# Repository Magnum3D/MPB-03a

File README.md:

MPB-03a
===========
Reprap Electronics for Magnum printers based on Printrboard

Отличия платы:

1. Плата питается напряжением 24 вольта (стол, экструдер и двигатели)
2. Установлен ЦАП для регулировки тока двигателей командами G-кода (как в версии F и исправлены ошибки).
3. Для питания вентиляторов добавлен дополнительный импульсный преобразователь на 12 вольт
4. Добавлено 4 мосфета с обвязкой - 2 для вентиляторов и 2 для светодиодных лент.
5. Заменены разъемы питания и нагревательного стола на мощные разъемы Molex.
6. Добавлен внешний разъем DSUB и на него выведено питание, ножки процессора и шина I2C
7. Мелкие исправления, доработки.

Постоянно ведется работа над усовершенствованием и доработкой платы, поэтому версия установленная в конкретный эксземпляр принтера может незначительно отличаться.

For more info see the Reprap wiki page http://reprap.org/wiki/Printrboard

The BoM with Digikey P/N's is available here: http://goo.gl/hQNEm

This project, and all of its design files (including the layout), is licensed under the [Creative Commons Attribution-ShareAlike 3.0 Unported](http://creativecommons.org/licenses/by-sa/3.0/) license.

Anyone found to be in violation of this license may not produce or discribute any products using these designs, and will have legal action taken against them.

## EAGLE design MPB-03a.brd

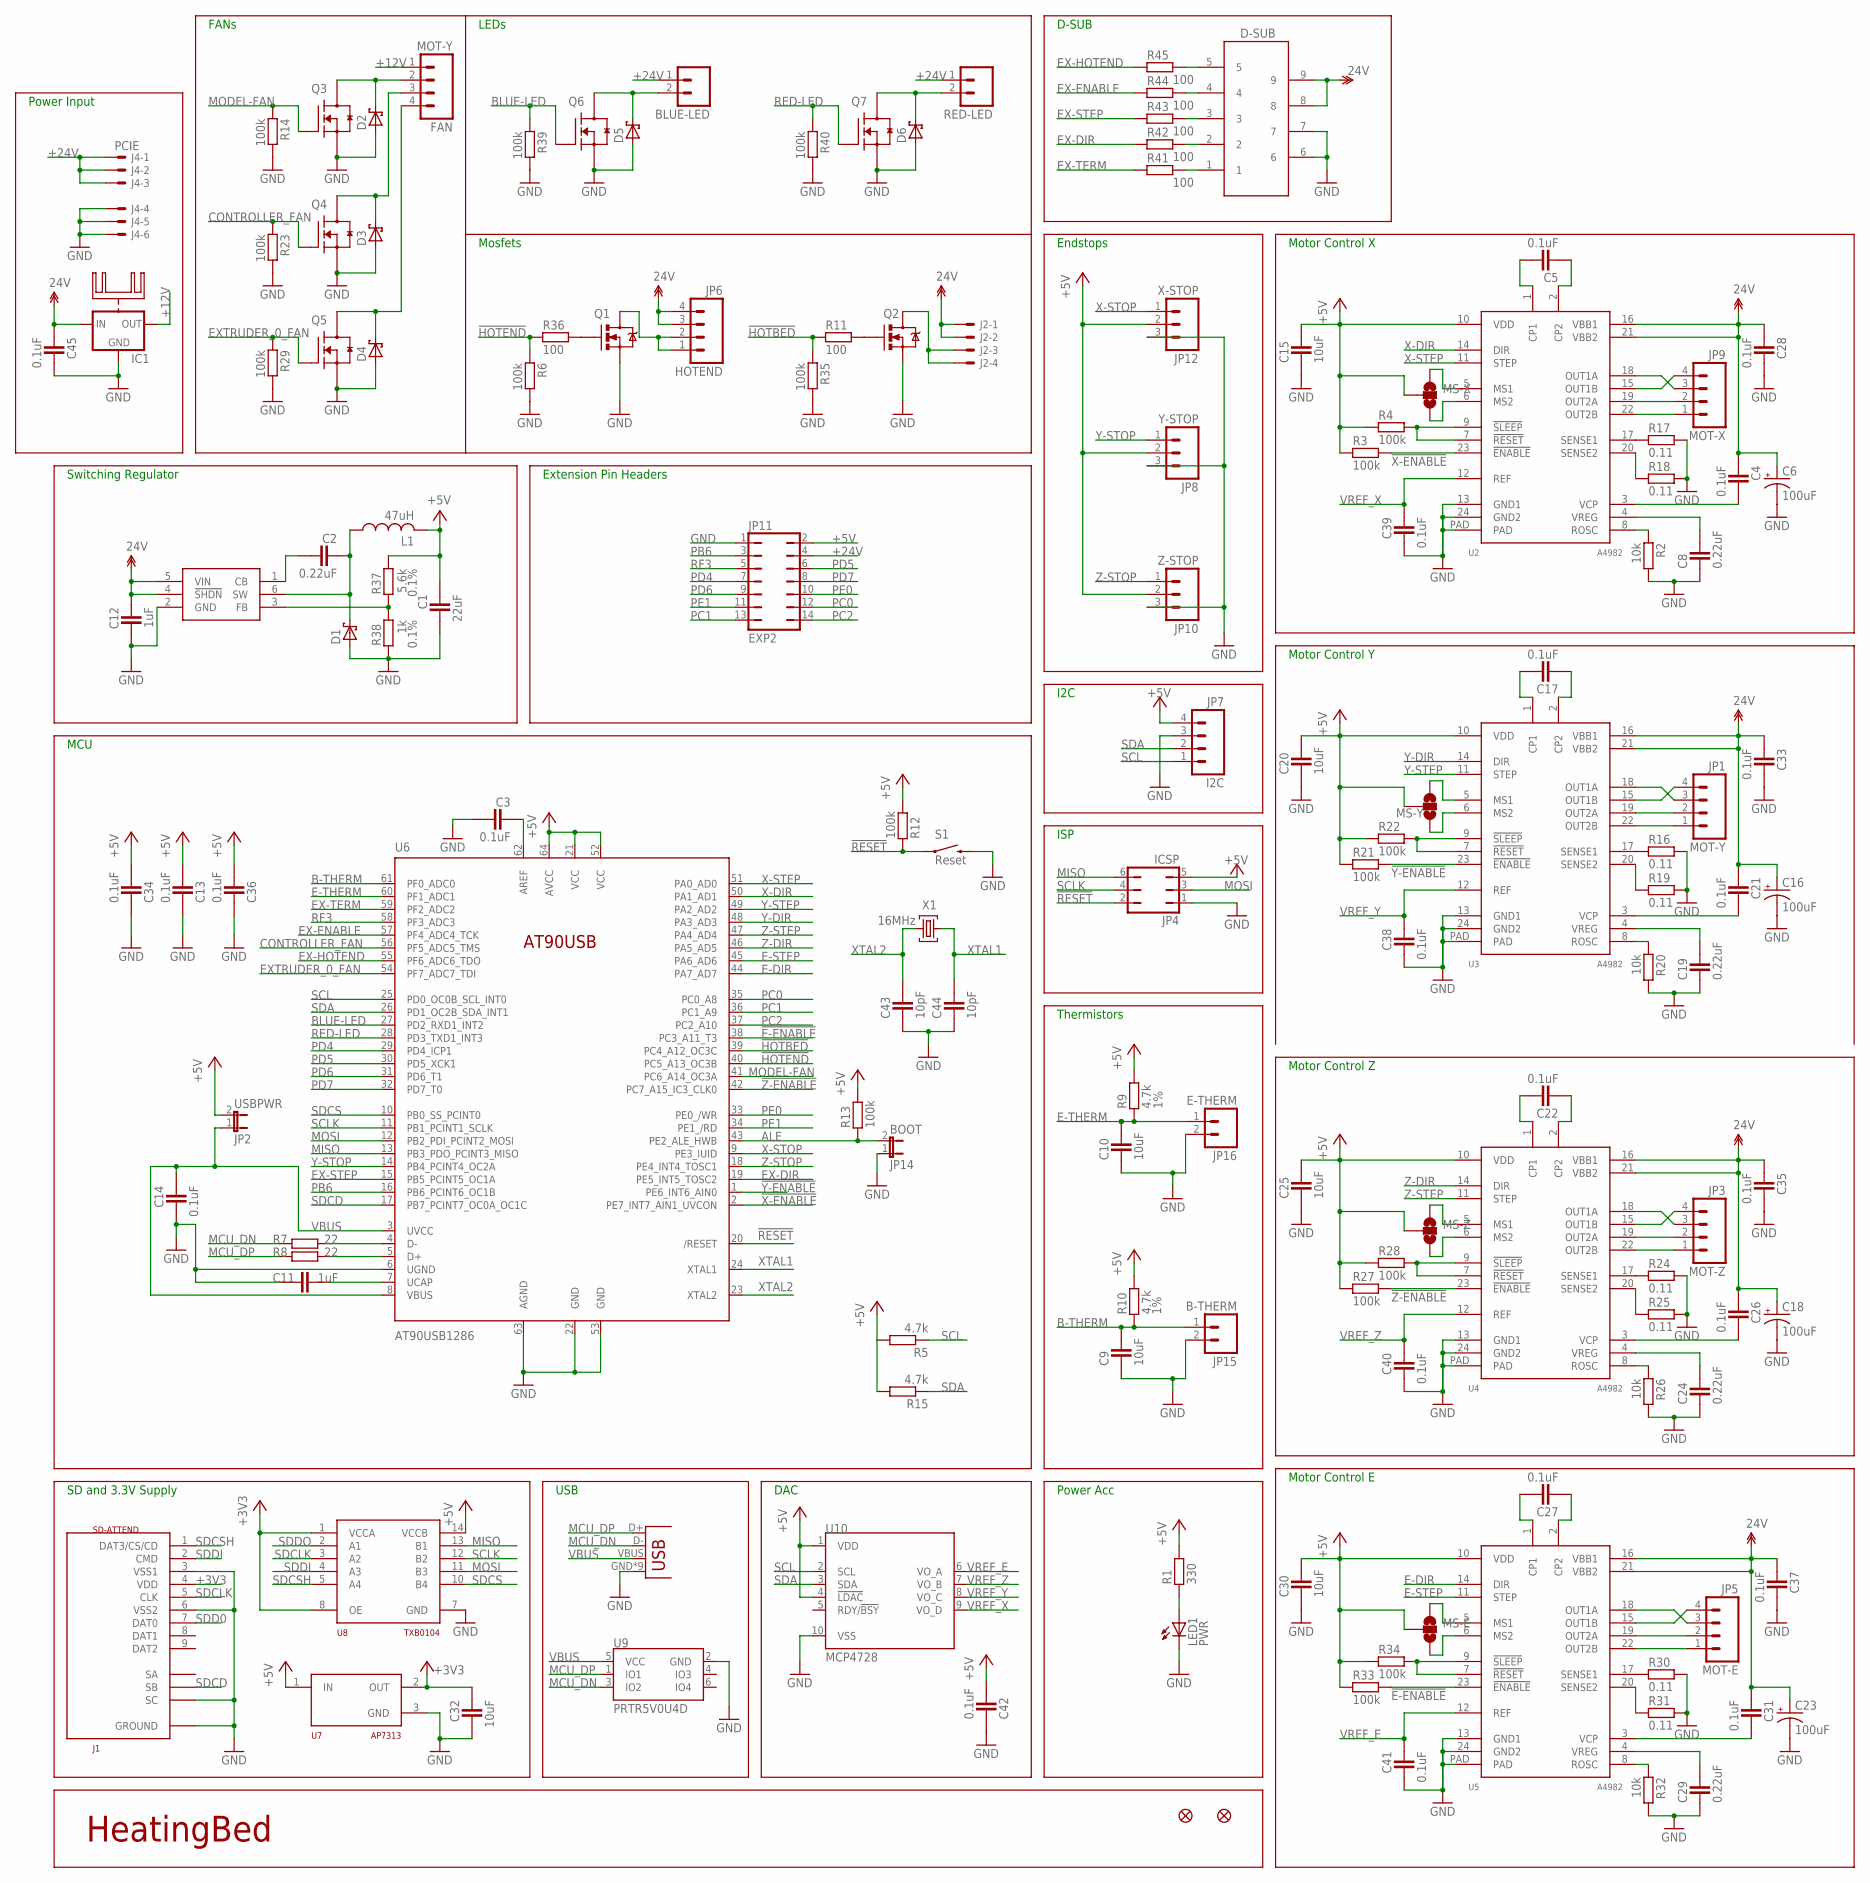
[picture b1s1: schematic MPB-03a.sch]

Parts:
BLUE-LED: M02POLAR; MOLEX-1X2
C1: 22uF; CAPC2012X145AN
C2, C8, C19, C24, C29: 0.22uF; CAPC2012X145AN
C3, C4, C5, C13, C14, C17, C21, C22, C26, C27, C28, C31, C33, C34, C35, C36, C37, C38, C39, C40, C41, C42, C45: 0.1uF; CAPC2012X145AN
C6, C16, C18, C23: 100uF; PANASONIC_D
C9, C10, C15, C20, C25, C30, C32: 10uF; CAPC2012X145AN
C11, C12: 1uF; CAPC2012X145AN
C43, C44: 10pF; CAPC2012X145AN
D1, D2, D3, D4, D5, D6: SCH-DIODESMA; SMA
D-SUB: 618009211721
FAN: MOT-Y; MOLEX-1X4
IC1: 78XXH; TO220-15X17X25
J1: SD-ATTEND
J2: 5566-4
J3: USB-MICRO-PTH; USB-MICROB-PTH
J4: PCIE; 5566-6
JP1: MOT-Y; MOLEX-1X4
JP2: USBPWR; 1X02
JP3: MOT-Z; MOLEX-1X4
JP4: ICSP; JP3Q
JP5: MOT-E; MOLEX-1X4
JP6: HOTEND; MOLEX-1X4
JP7: I2C; MOLEX-1X4
JP8: Y-STOP; MOLEX-1X3
JP9: MOT-X; MOLEX-1X4
JP10: Z-STOP; MOLEX-1X3
JP11: EXP2; JP7Q
JP12: X-STOP; MOLEX-1X3
JP14: BOOT; 1X02
JP15: B-THERM; 1X02
JP16: E-THERM; 1X02
JP26, JP33: FIDUCIAL1X2.5; FIDUCIAL-1X2.5
L1: 47uH; SDR1006
LED1: PWR; CHIP-LED0805
MS-E: SOLDERJUMPER_2WAYCONNECTED; SJ_3_CONNECTED
MS-X: SOLDERJUMPER_2WAYCONNECTED; SJ_3_CONNECTED
MS-Y: SOLDERJUMPER_2WAYCONNECTED; SJ_3_CONNECTED
MS-Z: SOLDERJUMPER_2WAYCONNECTED; SJ_3_CONNECTED
Q1, Q2: RFP30N06LE; TO220V
Q3, Q4, Q5, Q6, Q7: RFP30N06LE; SOT95P280X135-3N
R1: 330; RESC2012X70N
R2, R20, R26, R32: 10k; RESC2012X70N
R3, R4, R6, R12, R13, R14, R21, R22, R23, R27, R28, R29, R33, R34, R35, R39, R40: 100k; RESC2012X70N
R5, R15: 4.7k; RESC2012X70N
R7, R8: 22; RESC2012X70N
R9, R10: 4.7k; RESC2012X70N; TOLERANCE 1%
R11, R36, R41, R42, R43, R44, R45: 100; RESC2012X70N
R16, R17, R18, R19, R24, R25, R30, R31: 0.11; RESC2012X70N
R37: 5.6k; RESC2012X70N; TOLERANCE 0.1%
R38: 1k; RESC2012X70N; TOLERANCE 0.1%
RED-LED: M02POLAR; MOLEX-1X2
S1: Reset; TACTILE_SWITCH_TALL
U1: LM2841; TSOT6
U2, U3, U4, U5: A4982; TSSOP-24
U6: AT90USB1286; TQFP64-2
U7: AP7313; SOT23C
U8: TXB0104; TSSOP14
U9: PRTR5V0U4D; SOT23-6
U10: MCP4728; MSOP10
X1: 16MHz; NDK-XTAL

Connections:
!E-ENABLE: R33.2, U5.23 (!ENABLE), U6.38 (PC3_A11_T3)
!HOTBED: R11.1, R35.1, U6.39 (PC4_A12_OC3C)
!HOTEND: R6.1, R36.1, U6.40 (PC5_A13_OC3B)
!RESET: JP4.2, R12.1, S1.A2 (1), U6.20 (/RESET)
!X-ENABLE: R3.2, U2.23 (!ENABLE), U6.2 (PE7_INT7_AIN1_UVCON)
!Y-ENABLE: R21.2, U3.23 (!ENABLE), U6.1 (PE6_INT6_AIN0)
!Z-ENABLE: R27.2, U4.23 (!ENABLE), U6.42 (PC7_A15_IC3_CLK0)
+3V3: C32.1, J1.4 (VDD), U7.2 (OUT), U8.1 (VCCA), U8.8 (OE)
+5V: C1.1, C13.2, C15.2, C20.2, C25.2, C30.2, C34.2, C36.2, C42.2, JP2.2, JP4.5, JP7.4, JP8.2, JP10.2, JP11.2, JP12.2, L1.P$2 (2), MS-E.2, MS-X.2, MS-Y.2, MS-Z.2, R1.2, R3.1, R4.1, R5.2, R9.2, R10.2, R12.2, R13.2, R15.2, R21.1, R22.1, R27.1, R28.1, R33.1, R34.1, R37.1, U2.10 (VDD), U3.10 (VDD), U4.10 (VDD), U5.10 (VDD), U6.21 (VCC), U6.52 (VCC), U6.64 (AVCC), U7.1 (IN), U8.14 (VCCB), U10.1 (VDD), U10.4 (!LDAC)
+12V: FAN.1, IC1.OUT
+24V: BLUE-LED.1, C4.1, C6.+, C12.1, C16.+, C18.+, C21.1, C23.+, C26.1, C28.1, C31.1, C33.1, C35.1, C37.1, C45.1, D-SUB.8, D-SUB.9, IC1.IN, J2.1, J2.2, J4.1, J4.2, J4.3, JP6.3, JP6.4, JP11.4, RED-LED.1, U1.4 (!SHDN), U1.5 (VIN), U2.16 (VBB1), U2.21 (VBB2), U3.16 (VBB1), U3.21 (VBB2), U4.16 (VBB1), U4.21 (VBB2), U5.16 (VBB1), U5.21 (VBB2)
ALE: JP14.2, R13.1, U6.43 (PE2_ALE_HWB)
AREF: C3.1, U6.62 (AREF)
B-THERM: C9.2, JP15.1, R10.1, U6.61 (PF0_ADC0)
BLUE-LED: Q6.1 (G), R39.1, U6.27 (PD2_RXD1_INT2)
CONTROLLER_FAN: Q4.1 (G), R23.1, U6.56 (PF5_ADC5_TMS)
E-DIR: U5.14 (DIR), U6.44 (PA7_AD7)
E-STEP: U5.11 (STEP), U6.45 (PA6_AD6)
E-THERM: C10.2, JP16.1, R9.1, U6.60 (PF1_ADC1)
EX-DIR: R42.1, U6.19 (PE5_INT5_TOSC2)
EX-ENABLE: R44.1, U6.57 (PF4_ADC4_TCK)
EX-HOTEND: R45.1, U6.55 (PF6_ADC6_TDO)
EX-STEP: R43.1, U6.15 (PB5_PCINT5_OC1A)
EX-TERM: R41.1, U6.59 (PF2_ADC2)
EXTRUDER_0_FAN: Q5.1 (G), R29.1, U6.54 (PF7_ADC7_TDI)
GND: C1.2, C3.2, C6.-, C8.1, C9.1, C10.1, C11.1, C12.2, C13.1, C14.2, C15.1, C16.-, C18.-, C19.1, C20.1, C23.-, C24.1, C25.1, C28.2, C29.1, C30.1, C32.2, C33.2, C34.1, C35.2, C36.1, C37.2, C38.2, C39.2, C40.2, C41.2, C42.1, C43.1, C44.1, C45.2, D1.A, D2.A, D3.A, D4.A, D5.A, D6.A, D-SUB.6, D-SUB.7, IC1.GND, J1.3 (VSS1), J1.6 (VSS2), J1.G (GROUND), J1.SC, J3.GND, J3.GND1 (GND), J3.GND2 (GND), J3.GND3 (GND), J3.GND4 (GND), J3.GND5 (GND), J3.GND6 (GND), J3.GND7 (GND), J3.GND8 (GND), J4.4, J4.5, J4.6, JP4.1, JP7.3, JP8.3, JP10.3, JP11.1, JP12.3, JP14.1, JP15.2, JP16.2, LED1.C, Q1.3 (S), Q2.3 (S), Q3.2 (S), Q4.2 (S), Q5.2 (S), Q6.2 (S), Q7.2 (S), R2.2, R6.2, R14.2, R16.2, R17.2, R18.2, R19.2, R20.2, R23.2, R24.2, R25.2, R26.2, R29.2, R30.2, R31.2, R32.2, R35.2, R38.2, R39.2, R40.2, S1.B2 (2), U1.2 (GND), U2.13 (GND1), U2.24 (GND2), U2.PAD, U3.13 (GND1), U3.24 (GND2), U3.PAD, U4.13 (GND1), U4.24 (GND2), U4.PAD, U5.13 (GND1), U5.24 (GND2), U5.PAD, U6.6 (UGND), U6.22 (GND), U6.53 (GND), U6.63 (AGND), U7.3 (GND), U8.7 (GND), U9.2 (GND), U10.10 (VSS)
HOTBED-GND: J2.3, J2.4, Q2.2 (D)
HOTEND-GND: JP6.1, JP6.2, Q1.2 (D)
MCU_DN: J3.D-, R7.1, U9.3 (IO2)
MCU_DP: J3.D+, R8.1, U9.1 (IO1)
MISO: JP4.6, U6.13 (PB3_PDO_PCINT3_MISO), U8.13 (B1)
MODEL-FAN: Q3.1 (G), R14.1, U6.41 (PC6_A14_OC3A)
MOSI: JP4.3, U6.12 (PB2_PDI_PCINT2_MOSI), U8.11 (B3)
unnamed: LED1.A, R1.1
unnamed: D2.C, FAN.2, Q3.3 (D)
unnamed: R7.2, U6.4 (D-)
unnamed: R8.2, U6.5 (D+)
unnamed: D3.C, FAN.3, Q4.3 (D)
unnamed: D4.C, FAN.4, Q5.3 (D)
unnamed: Q2.1 (G), R11.2
unnamed: BLUE-LED.2, D5.C, Q6.3 (D)
unnamed: C11.2, U6.7 (UCAP)
unnamed: JP9.3, U2.18 (OUT1A)
unnamed: C5.2, U2.1 (CP1)
unnamed: C5.1, U2.2 (CP2)
unnamed: R2.1, U2.8 (ROSC)
unnamed: R17.1, U2.17 (SENSE1)
unnamed: R18.1, U2.20 (SENSE2)
unnamed: C4.2, U2.3 (VCP)
unnamed: JP9.4, U2.15 (OUT1B)
unnamed: D-SUB.5, R45.2
unnamed: C8.2, U2.4 (VREG)
unnamed: JP9.2, U2.19 (OUT2A)
unnamed: R4.2, U2.7 (!RESET), U2.9 (!SLEEP)
unnamed: R37.2, R38.1, U1.3 (FB)
unnamed: JP9.1, U2.22 (OUT2B)
unnamed: JP1.2, U3.19 (OUT2A)
unnamed: JP1.1, U3.22 (OUT2B)
unnamed: JP1.4, U3.15 (OUT1B)
unnamed: MS-X.1, U2.5 (MS1)
unnamed: MS-X.3, U2.6 (MS2)
unnamed: C17.2, U3.1 (CP1)
unnamed: C17.1, U3.2 (CP2)
unnamed: JP1.3, U3.18 (OUT1A)
unnamed: R19.1, U3.20 (SENSE2)
unnamed: D6.C, Q7.3 (D), RED-LED.2
unnamed: R20.1, U3.8 (ROSC)
unnamed: C19.2, U3.4 (VREG)
unnamed: R22.2, U3.7 (!RESET), U3.9 (!SLEEP)
unnamed: C21.2, U3.3 (VCP)
unnamed: R16.1, U3.17 (SENSE1)
unnamed: JP3.4, U4.15 (OUT1B)
unnamed: JP3.3, U4.18 (OUT1A)
unnamed: JP3.2, U4.19 (OUT2A)
unnamed: MS-Y.1, U3.5 (MS1)
unnamed: MS-Y.3, U3.6 (MS2)
unnamed: C22.2, U4.1 (CP1)
unnamed: C22.1, U4.2 (CP2)
unnamed: R24.1, U4.17 (SENSE1)
unnamed: R25.1, U4.20 (SENSE2)
unnamed: R26.1, U4.8 (ROSC)
unnamed: C24.2, U4.4 (VREG)
unnamed: R28.2, U4.7 (!RESET), U4.9 (!SLEEP)
unnamed: C26.2, U4.3 (VCP)
unnamed: JP3.1, U4.22 (OUT2B)
unnamed: JP5.4, U5.15 (OUT1B)
unnamed: JP5.3, U5.18 (OUT1A)
unnamed: JP5.2, U5.19 (OUT2A)
unnamed: MS-Z.1, U4.5 (MS1)
unnamed: MS-Z.3, U4.6 (MS2)
unnamed: C27.2, U5.1 (CP1)
unnamed: C27.1, U5.2 (CP2)
unnamed: R30.1, U5.17 (SENSE1)
unnamed: R31.1, U5.20 (SENSE2)
unnamed: D-SUB.4, R44.2
unnamed: R32.1, U5.8 (ROSC)
unnamed: C29.2, U5.4 (VREG)
unnamed: R34.2, U5.7 (!RESET), U5.9 (!SLEEP)
unnamed: C31.2, U5.3 (VCP)
unnamed: JP5.1, U5.22 (OUT2B)
unnamed: D-SUB.3, R43.2
unnamed: D-SUB.2, R42.2
unnamed: Q1.1 (G), R36.2
unnamed: MS-E.1, U5.5 (MS1)
unnamed: MS-E.3, U5.6 (MS2)
unnamed: D-SUB.1, R41.2
unnamed: C2.1, D1.C, L1.P$1 (1), U1.6 (SW)
unnamed: C2.2, U1.1 (CB)
PB6: JP11.3, U6.16 (PB6_PCINT6_OC1B)
PC0: JP11.12, U6.35 (PC0_A8)
PC1: JP11.13, U6.36 (PC1_A9)
PC2: JP11.14, U6.37 (PC2_A10)
PD4: JP11.7, U6.29 (PD4_ICP1)
PD5: JP11.6, U6.30 (PD5_XCK1)
PD6: JP11.9, U6.31 (PD6_T1)
PD7: JP11.8, U6.32 (PD7_T0)
PE0: JP11.10, U6.33 (PE0_/WR)
PE1: JP11.11, U6.34 (PE1_/RD)
RED-LED: Q7.1 (G), R40.1, U6.28 (PD3_TXD1_INT3)
RF3: JP11.5, U6.58 (PF3_ADC3)
SCL: JP7.1, R5.1, U6.25 (PD0_OC0B_SCL_INT0), U10.2 (SCL)
SCLK: JP4.4, U6.11 (PB1_PCINT1_SCLK), U8.12 (B2)
SDA: JP7.2, R15.1, U6.26 (PD1_OC2B_SDA_INT1), U10.3 (SDA)
SDCD: J1.SB, U6.17 (PB7_PCINT7_OC0A_OC1C)
SDCLK: J1.5 (CLK), U8.3 (A2)
SDCS: U6.10 (PB0_SS_PCINT0), U8.10 (B4)
SDCSH: J1.1 (DAT3/CS/CD), U8.5 (A4)
SDD0: J1.7 (DAT0)
SDDI: J1.2 (CMD), U8.4 (A3)
SDDO: U8.2 (A1)
VBUS: C14.1, J3.VBUS, JP2.1, U6.3 (UVCC), U6.8 (VBUS), U9.5 (VCC)
VREF_E: C41.1, U5.12 (REF), U10.6 (VO_A)
VREF_X: C39.1, U2.12 (REF), U10.9 (VO_D)
VREF_Y: C38.1, U3.12 (REF), U10.8 (VO_C)
VREF_Z: C40.1, U4.12 (REF), U10.7 (VO_B)
X-DIR: U2.14 (DIR), U6.50 (PA1_AD1)
X-STEP: U2.11 (STEP), U6.51 (PA0_AD0)
X-STOP: JP12.1, U6.9 (PE3_IUID)
XTAL1: C44.2, U6.24 (XTAL1), X1.P$1 (1)
XTAL2: C43.2, U6.23 (XTAL2), X1.P$2 (2)
Y-DIR: U3.14 (DIR), U6.48 (PA3_AD3)
Y-STEP: U3.11 (STEP), U6.49 (PA2_AD2)
Y-STOP: JP8.1, U6.14 (PB4_PCINT4_OC2A)
Z-DIR: U4.14 (DIR), U6.46 (PA5_AD5)
Z-STEP: U4.11 (STEP), U6.47 (PA4_AD4)
Z-STOP: JP10.1, U6.18 (PE4_INT4_TOSC1)

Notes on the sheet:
Motor Control X
Motor Control Y
Motor Control Z
Motor Control E
ISP
Thermistors
Endstops
Mosfets
Power Acc
HeatingBed
Extension Pin Headers
Switching Regulator
SD and 3.3V Supply
Power Input
MCU
I2C
USB
DAC
FANs
LEDs
D-SUB

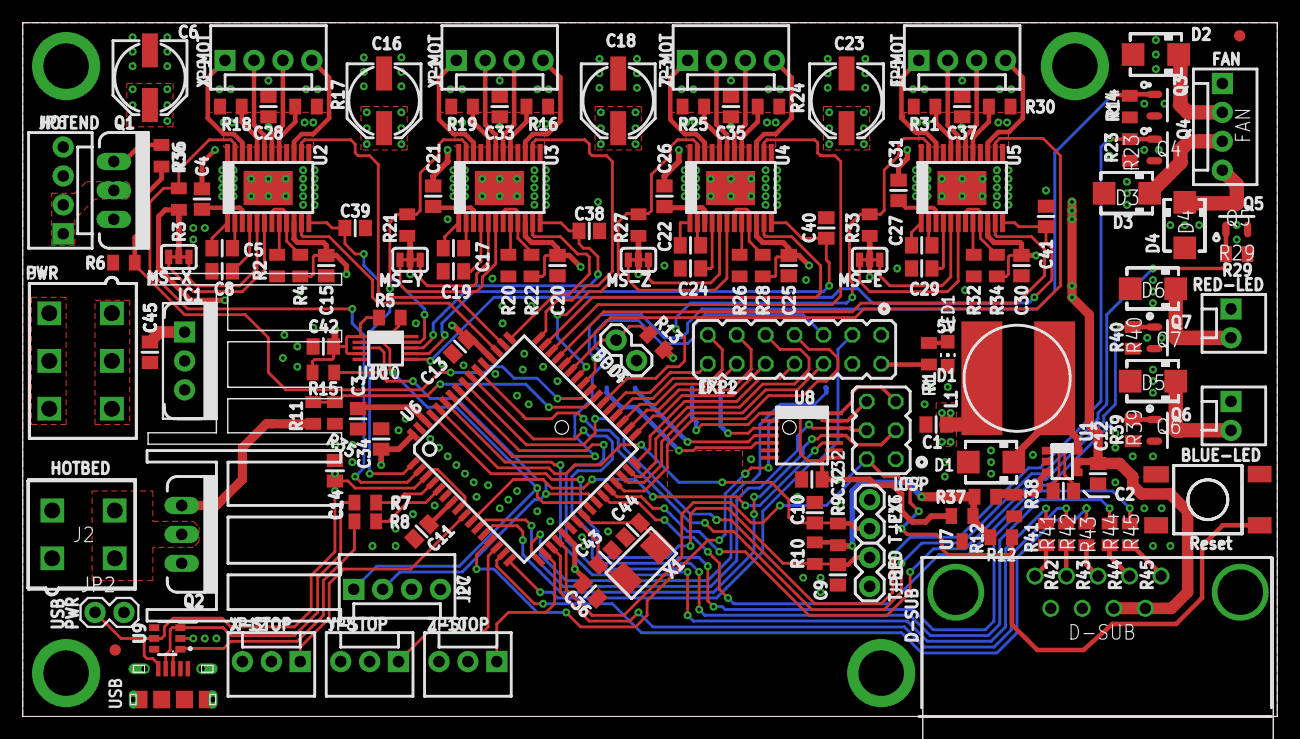
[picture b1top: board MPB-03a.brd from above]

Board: 4 copper layers, 110.2 x 61.0 mm, 146 parts (1 on the bottom side), 144 nets.

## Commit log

2014-12-26 Rename
2014-12-26 Добавлены исходные файлы проекта.
2014-12-26 Обновлено описание платы.

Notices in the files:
parts and their libraries:
D-SUB_Connectors: Copyright: Würth Elektronik
